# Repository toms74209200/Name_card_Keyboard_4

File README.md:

# Study 4 Scarlet

- 4 Keyboard
- Kailh Choc type
- Business card size(91mm x 55mm)
- arduino(Pro micro) compatible
- USB type-C interface

## Usage

See [User guide (English)](./docs/user_guide_en.md) ([日本語](./docs/user_guide_ja.md)). 

## License

MIT License

## Author

[toms74209200](<https://github.com/toms74209200>)

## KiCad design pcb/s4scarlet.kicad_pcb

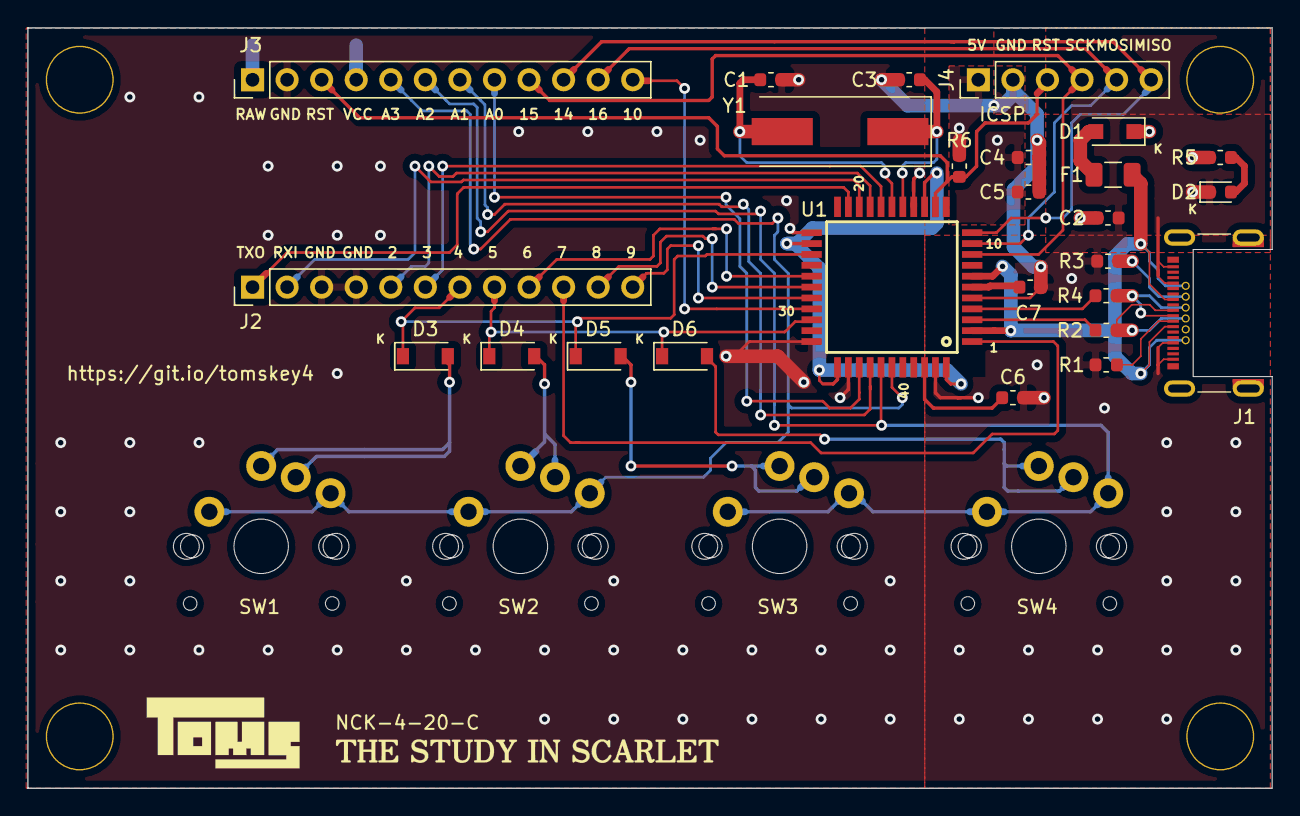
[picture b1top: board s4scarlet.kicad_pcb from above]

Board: 2 copper layers, 91.4 x 55.9 mm, 34 parts (0 on the bottom side), 38 nets.

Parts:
C1, C3: 22p; C_0603_1608Metric
C2: 10u; C_0603_1608Metric
C4, C7: 1u; C_0603_1608Metric
C5, C6: 0.1u; C_0603_1608Metric
D1: RB161MM-20; D_SOD-123F
D2: SMLE13WBC8W1; LED_0603_1608Metric
D3, D4, D5, D6: 1N4148W; D_SOD-123
F1: NANOSMDC050F/13.2; Fuse_1206_3216Metric
J1: CX70M-24P1; USB-C_Female_CX70M-24P1
J2, J3: Conn_01x12_Female; PinHeader_1x12_P2.54mm_Vertical
J4: Conn_01x06_Female; PinHeader_1x06_P2.54mm_Vertical
R1, R2, R3, R4: 22; R_0603_1608Metric
R5: 1k; R_0603_1608Metric
R6: 10k; R_0603_1608Metric
Ref**: Val**; HOLE
Ref**#2, Ref**#3, Ref**#4: Val**; HOLE
SW1, SW2, SW3, SW4: SW_Push; CherryMX_Choc_1u
U1: ATmega32U4-AU; ATMEGA32U4-AU
Y1: 16MHz; Crystal_SMD_HC49-SD

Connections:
+5V: C2.1, C4.1, C5.1, D1.1, J3.1, J3.4, J4.1, R5.1, R6.2, U1.14, U1.24, U1.34, U1.44
/A0: J3.8, U1.36
/A1: J3.7, U1.37
/A2: J3.6, SW3.1, SW4.1, U1.38
/A3: J3.5, SW1.1, SW2.1, U1.39
/D2: J2.5, U1.19
/D3: J2.6, U1.18
/D4: D3.1, D5.1, J2.7, U1.25
/D5: D4.1, D6.1, J2.8, U1.31
/D6: J2.9, U1.27
/D7: J2.10, U1.1
/D8: J2.11, U1.28
/D9: J2.12, U1.29
/D10: J3.12, U1.30
/D+: R4.1, U1.4
/D-: R2.1, U1.3
/MISO: J3.10, J4.6, U1.11
/MOSI: J3.11, J4.5, U1.10
/RESET: J3.3, J4.3, R6.1, U1.13
/RXL: J2.2, U1.20
/SCK: J3.9, J4.4, U1.9
/TXO: J2.1, U1.21
GNDPWR: C1.2, C2.2, C3.2, C4.2, C5.2, C6.2, C7.2, D2.1, J1.A1, J1.A12, J1.B1, J1.B12, J2.3, J2.4, J3.2, J4.2, R1.1, R3.1, U1.5, U1.15, U1.23, U1.33, U1.35, U1.43
unnamed: C1.1, U1.17, Y1.2
unnamed: C3.1, U1.16, Y1.1
unnamed: C6.1, U1.42
unnamed: C7.1, U1.6
unnamed: D1.2, F1.1
unnamed: D2.2, R5.2
unnamed: D3.2, SW1.2
unnamed: D4.2, SW2.2
unnamed: D5.2, SW3.2
unnamed: D6.2, SW4.2
unnamed: J1.A5, R1.2
unnamed: J1.A6, J1.B6, R4.2
unnamed: J1.A7, J1.B7, R2.2
unnamed: J1.B5, R3.2
VCC: F1.2, J1.A4, J1.A9, J1.B4, J1.B9, U1.2, U1.7

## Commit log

2020-06-14 [add]add first, PCB
2020-06-18 [change]change AW
2020-06-18 [add]add gerber
2020-06-22 [add]add drill gerber data
2020-07-02 [docs]add user guide
2020-07-02 [change]conmine drillgerber data
2020-07-04 [add]add pin assign
2020-07-19 [fix]fix USB data signal
2020-07-26 [change]update pcb
2020-08-11 [clean]rename
2020-08-13 [add]add firmware
2020-08-17 [docs]add usage of user guide
2020-08-20 [fix]change PD value of USB CC pins
